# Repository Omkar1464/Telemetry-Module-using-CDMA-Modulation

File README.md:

# Long Range Telemetry Module (Phase-I)

[-purple.svg)](#firmware-architecture--timing)

> **B.Tech Phase-I Project Report & Codebase**  
> **Department of Electronics Engineering**, Sardar Vallabhbhai National Institute of Technology (SVNIT), Surat  
> **Academic Year:** 2025–26 | **Project Group:** G60  
> **Project Guide:** Dr. Suresh Dahiya (Assistant Professor, DoECE)  
> **Authors:** Moksha Parikh (`U23EC001`), Ridham Chaudhary (`U23EC030`), Omkar Sinh (`U23EC048`)

---

## 📌 Overview

This repository contains the embedded firmware, circuit schematics, simulation models, and validation benchmarks for the **Long Range Telemetry Module (Phase-I)** designed for high-altitude drone and UAV/CanSat payload communication.

Operating under the severe resource constraints of an 8-bit **ATmega328P** microcontroller (16 MHz clock, 2 KB SRAM), the system implements a **Direct Sequence Spread Spectrum (DSSS) / Code Division Multiple Access (CDMA)** baseband transmitter alongside a discrete 433 MHz RF front-end architecture.

### Key Capabilities
- **Dual-Channel CDMA Modulation:**
  - **In-Phase (I) Channel:** Carries GPS navigation data ($f_d = 100\text{ Hz}$) spread by a 1000-chip PRN sequence ($N = 1000$, theoretical processing gain $G_p = 30\text{ dB}$).
  - **Quadrature (Q) Channel:** Carries high-rate environmental telemetry ($f_d = 10\text{ kHz}$) spread by a 10-chip sequence ($N = 10$).
- **Cycle-Accurate 100 kHz Baseband Chip Rate:** $10.0\ \mu\text{s}$ per chip generated through Direct Port Manipulation (DPM), interrupt jitter elimination, and deterministic cycle calibration.
- **RF Front-End Design & Simulation:** Colpitts Local Oscillator (MPSH10 BJT) and dual-gate MOSFET (BF998) mixer stage simulated in NI Multisim and laid out on a custom 2-layer mixed-signal PCB in KiCad.

---

## 🏗️ System Architecture

```
                       +------------------------------+
                       |      2.5V - 3V Battery       |
                       +--------------+---------------+
                                      |
                            [DC-DC Boost Converter]
                                      |
                 +--------------------+--------------------+
                 | (3.3V / 5V Logic)                       | (Vcc RF)
                 v                                         v
+------------------------------------+    +----------------------------------+
|           Sensors & Inputs         |    |        Discrete RF Chain         |
| - u-blox NEO-6M GPS (UART @ 9600)  |    | - MPSH10 Colpitts LO (~358 MHz)  |
| - SHT-40 Humidity & Temp (I2C)     |    | - Dual BF998 MOSFET Mixers       |
| - PT1000-S Platinum RTD (I2C)      |    | - SAW Filter FL1 (433.92 MHz)    |
| - On-board NTC Thermistor (ADC)    |    | - RD01MUS2B RF Power Amplifier   |
+-----------------+------------------+    | - Pi-Matching Network & SMA Port |
                  |                        +-----------------+----------------+
                  v                                          ^
+------------------------------------+                       |
|       ATmega328P Controller        |                       |
| - LFSR PRN Generator (10-bit)      |                       |
| - 8x Bit-Packed Memory Storage     |                       |
| - Single-Cycle Port Writes (DPM)   |                       |
+--------+--------------------+------+                       |
         | (Dout-1: I-Chan)   | (Dout-2: Q-Chan)             |
         +--------------------+------------------------------+
```

---

## 📂 Repository File Structure

| Folder / File | Description |
| :--- | :--- |
| `GPS-Neo6M/` | Arduino firmware for NEO-6M GPS NMEA sentence extraction, checksum validation, and coordinate parsing using TinyGPS++. |
| `I_trail/` & `I_trial1/` | Baseband firmware implementation for the I-Channel (1000-chip LFSR generation, bit-packing, cycle-accurate delay loops). |
| `Q_trail/` | Baseband firmware implementation for the Q-Channel (10-chip array spreading code, corrected timing loops). |
| `task1/` & `task2/` | Firmware test suites, sensor serialization routines, and hardware debugging logs. |
| `BF998 MOSFET LIB/` | Spice simulation libraries and component footprints for the BF998 dual-gate N-channel MOSFET. |
| `Datasheet/` | Technical documentation and datasheets for active and passive components (MPSH10, BF998, RD01MUS2B, NEO-6M, SHT-40). |
| `CDMA transferring rate.pdf` | Documentation on CDMA transmission speed, spreading factors, and modulation characteristics. |
| `G48- Update-LO Simulation...` | Report and simulation data for the Local Oscillator circuit. |
| `Design1.ms14` | NI Multisim top-level schematic and RF modulator simulation circuit. |
| `L_oscillator.ms14` | NI Multisim Colpitts oscillator simulation model. |
| `d2.ms14` & `d2out.scp` | Multisim circuit simulation and oscilloscope graph captures. |
| `oscillator.cir` | SPICE netlist for the Colpitts Local Oscillator stage. |

---

## ⚡ Firmware & Timing Engineering

### 1. Memory Optimization (8× SRAM Reduction)
The ATmega328P has only 2 KB of SRAM. Allocating 1000 chips as individual `uint8_t` bytes would consume 1000 bytes (almost 50% of total SRAM):
- **Solution:** Bit-packing stores 8 chips per byte, reducing the 1000-chip array to just **125 bytes** (`uint8_t I_CDMA_PACKED[125]`).
- **LFSR PRN Generator:** Generated dynamically at startup via a 10-bit LFSR using primitive polynomial $x_n = x_{n-10} \oplus x_{n-7}$ with initial seed `0x02DF`, eliminating large hardcoded arrays in flash memory.

### 2. Elimination of Interrupt Jitter & Direct Port Manipulation
- Standard Arduino `digitalWrite()` requires ~50–60 clock cycles.
- **Direct Port Manipulation (DPM)** writes directly to `PORTB`, changing pin states in a single clock cycle ($62.5\text{ ns}$ at $16\text{ MHz}$):
  ```cpp
  PORTB |=  (1 << PORTB2); // Set Pin 10 HIGH (1 cycle)
  PORTB &= ~(1 << PORTB2); // Set Pin 10 LOW  (1 cycle)
  ```
- The Arduino core timer (`Timer0`) introduces up to $2\ \mu\text{s}$ interrupt jitter every $1.024\text{ ms}$. This is eliminated by calling `noInterrupts()` before entering the continuous transmission loop.

### 3. Cycle-Accurate Calibration Loop
To achieve a target chip rate of $f_c = 100\text{ kHz}$ ($T_c = 10.0\ \mu\text{s}$):
$$\text{Total Clock Budget} = 10.0\ \mu\text{s} \times 16\text{ MHz} = 160\text{ cycles}$$
Accounting for loop overhead, bit shifting, and DPM write (~3 cycles), the calibrated delay is:
```cpp
__builtin_avr_delay_cycles(157); // 157 cycles @ 16 MHz = 9.81 us
```

---

## 🔬 Hardware Verification & Measurement Results

Because random PRN sequences produce consecutive identical chips that cause auto-counter readouts to fluctuate on oscilloscopes (the *PRN frequency illusion*), a **DSO Calibration Mode** with an alternating `0xAA` (`10101010b`) test pattern was used for hardware verification:
$$f_{\text{DSO}} = \frac{f_c}{2} = 50.0\text{ kHz}$$

| Parameter | Theoretical / Target | Measured (Tektronix DSO) | Timing Deviation |
| :--- | :---: | :---: | :---: |
| **I-Channel Baseline (Alternating)** | $50.0\text{ kHz}$ ($20.0\ \mu\text{s}$ period) | $45.89\text{ kHz}$ ($22.20\ \mu\text{s}$) | $-8.22\%$ |
| **Q-Channel Baseline (Post-Correction)**| $50.0\text{ kHz}$ ($20.0\ \mu\text{s}$ period) | $45.03\text{ kHz}$ ($22.20\ \mu\text{s}$) | $-9.94\%$ |
| **Single Chip Duration** | $10.0\ \mu\text{s}$ | $\approx 11.10\ \mu\text{s}$ | Within $\pm 10\%$ SDR budget |
| **Logic Level (Rail-to-Rail)** | $5.0\text{ V}$ | $5.60\text{ V} - 7.60\text{ V}_{\text{pk-pk}}$* | Rail-to-rail confirmed |

*\*Note: High peak-to-peak reading on the DSO is attributed to probe measurement ringing on the nanosecond-fast DPM rise/fall edges.*

---

## 📡 RF Front-End & PCB Design

- **Colpitts Local Oscillator:** Built with an **MPSH10 NPN BJT** ($f_T \approx 650\text{ MHz}$).
  $$C_{eq} = \frac{C_1 C_2}{C_1 + C_2} = \frac{22 \times 22}{22 + 22} = 11\text{ pF}$$
  $$f_0 = \frac{1}{2\pi \sqrt{L_2 \cdot C_{eq}}} = \frac{1}{2\pi \sqrt{0.18\ \mu\text{H} \cdot 11\text{ pF}}} \approx 358\text{ MHz}$$
- **Multisim Simulation:** Sustained oscillation confirmed at $357\text{ MHz}$ with an output amplitude of $3.54\text{ V}_{\text{pk}}$ ($< 0.3\%$ discrepancy from analytical equations).
- **Custom PCB (KiCad):** 2-layer mixed-signal board featuring segregated functional partitions:
  - Top-Right: NEO-6M GPS module placed near the perimeter for antenna clearance.
  - Top-Center: ATmega328P TQFP-32 with SPI header and adjacent clock crystal.
  - Left: Power management (NCP1640T, HT3608) and Local Oscillator.
  - Bottom-Right: RF chain with dual BF998 mixers, SAW filter, RD01MUS2B PA, and SMA connector backed by a solid stitched ground plane.

---

## 👥 Authors & Academic Affiliation

* **Moksha Parikh** (`U23EC001`) -- [GitHub Profile](https://github.com/mokshaparikh11)   
* **Ridham Chaudhary** (`U23EC030`) — [GitHub Profile](https://github.com/chaudharyridham)  
* **Omkar Sinh** (`U23EC048`) — [GitHub Profile](https://github.com/Omkar1464)  

**Project Guide:**  
**Dr. Suresh Dahiya**, Assistant Professor, Department of Electronics and Communication Engineering  
**Sardar Vallabhbhai National Institute of Technology (SVNIT)**, Surat, Gujarat, India.

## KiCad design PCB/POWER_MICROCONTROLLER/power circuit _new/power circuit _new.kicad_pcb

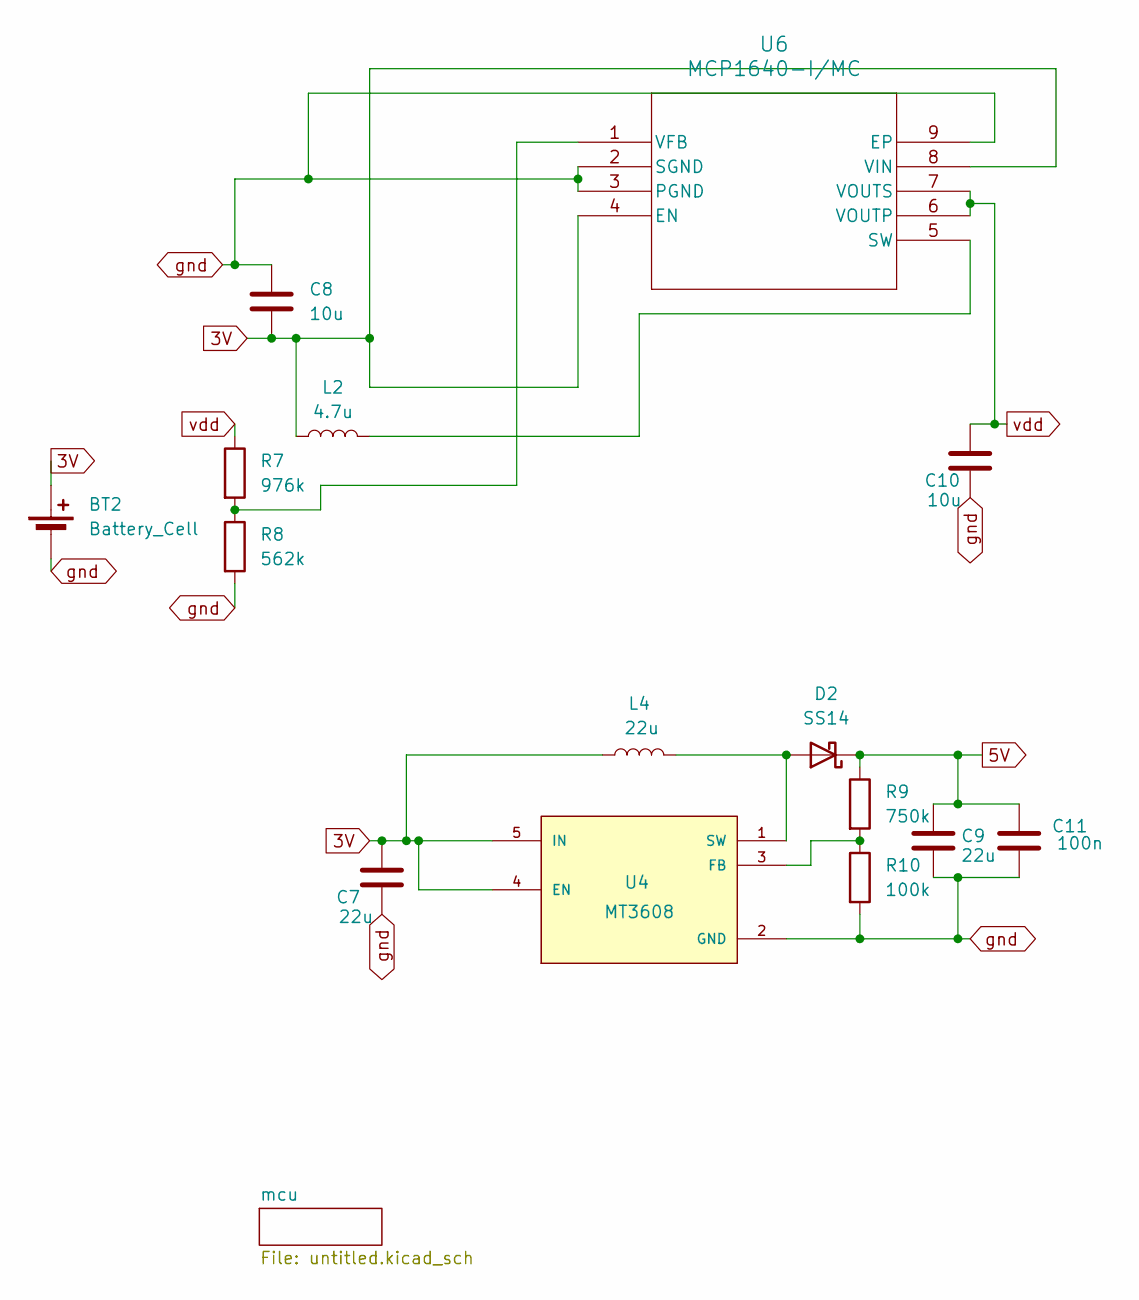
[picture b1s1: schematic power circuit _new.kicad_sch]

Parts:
BT2: Battery_Cell; SolderWire-0.25sqmm_1x02_P4.2mm_D0.65mm_OD1.7mm_Relief2x
C7, C9: 22u; C_0603_1608Metric
C8, C10: 10u; C_0603_1608Metric
C11: 100n; C_0603_1608Metric
D2: SS14; D_SMA
L2: 4.7u; L_0603_1608Metric
L4: 22u; L_0603_1608Metric
R7: 976k; R_0603_1608Metric
R8: 562k; R_0603_1608Metric
R9: 750k; R_0603_1608Metric
R10: 100k; R_0603_1608Metric
U4: MT3608; SOT95P280X145-6N; PARTREV 1.0
U6: MCP1640-I/MC; DFN8_2x3MC_MCH

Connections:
3V: BT2.1 (+), C7.1, C8.1, L2.1, L4.1, U4.4 (EN), U4.5 (IN), U6.4 (EN), U6.8 (VIN)
5V: C9.1, C11.1, D2.1 (K), R9.1
unnamed: D2.2 (A), L4.2, U4.1 (SW)
unnamed: R9.2, R10.1, U4.3 (FB)
unnamed: L2.2, U6.5 (SW)
unnamed: R7.2, R8.1, U6.1 (VFB)
gnd: BT2.2 (-), C7.2, C8.2, C9.2, C10.2, C11.2, R8.2, R10.2, U4.2 (GND), U6.2 (SGND), U6.3 (PGND), U6.9 (EP); also elsewhere on the board
vdd: C10.1, R7.1, U6.6 (VOUTP), U6.7 (VOUTS); also elsewhere on the board

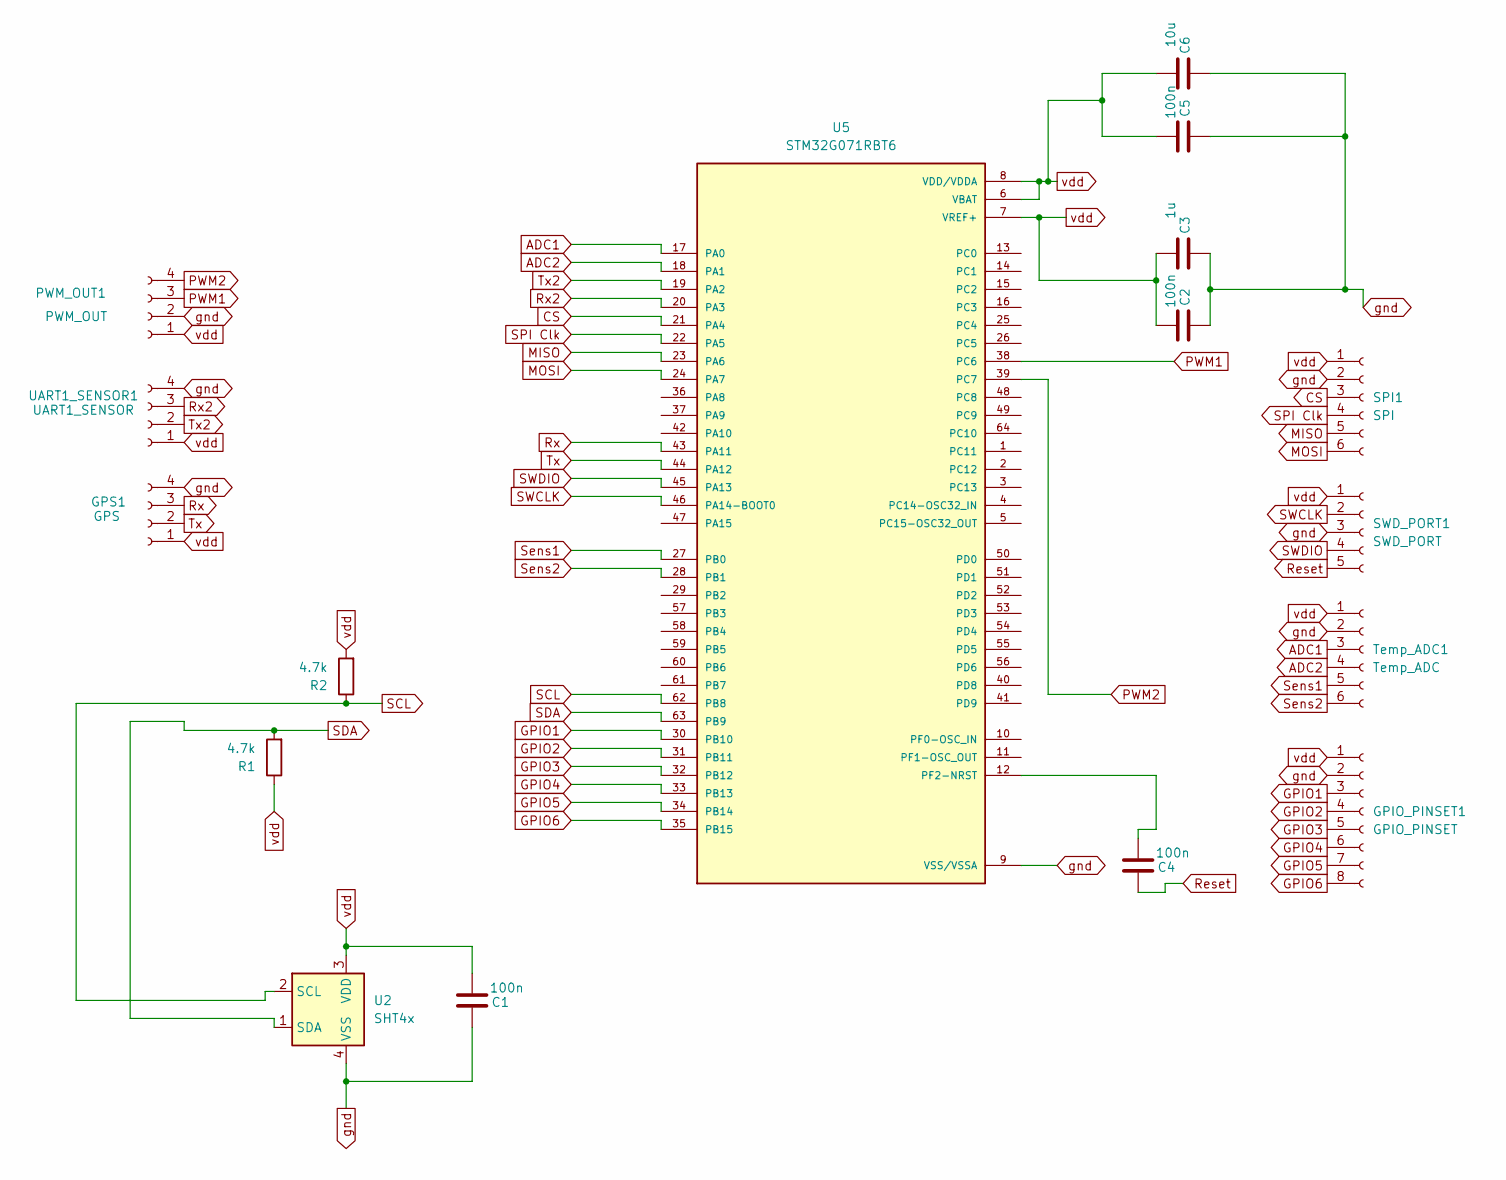
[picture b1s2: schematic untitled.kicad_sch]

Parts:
C1, C2, C4, C5: 100n; C_0603_1608Metric
C3: 1u; C_0603_1608Metric
C6: 10u; C_0603_1608Metric
GPIO_PINSET1: GPIO_PINSET; PinSocket_1x08_P2.54mm_Vertical
GPS1: GPS; PinSocket_1x04_P2.54mm_Vertical
PWM_OUT1: PWM_OUT; PinSocket_1x04_P2.54mm_Vertical
R1, R2: 4.7k; R_0603_1608Metric
SPI1: SPI; PinSocket_1x06_P2.54mm_Vertical
SWD_PORT1: SWD_PORT; PinSocket_1x05_P2.54mm_Vertical
Temp_ADC1: Temp_ADC; PinSocket_1x06_P2.54mm_Vertical
U2: SHT4x; Sensirion_DFN-4_1.5x1.5mm_P0.8mm_SHT4x_NoCentralPad
U5: STM32G071RBT6; LQFP-64_7x7mm_P0.4mm; PARTREV 2
UART1_SENSOR1: UART1_SENSOR; PinSocket_1x04_P2.54mm_Vertical

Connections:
ADC1: Temp_ADC1.3, U5.17 (PA0)
ADC2: Temp_ADC1.4, U5.18 (PA1)
CS: SPI1.3, U5.21 (PA4)
GPIO1: GPIO_PINSET1.3, U5.30 (PB10)
GPIO2: GPIO_PINSET1.4, U5.31 (PB11)
GPIO3: GPIO_PINSET1.5, U5.32 (PB12)
GPIO4: GPIO_PINSET1.6, U5.33 (PB13)
GPIO5: GPIO_PINSET1.7, U5.34 (PB14)
GPIO6: GPIO_PINSET1.8, U5.35 (PB15)
MISO: SPI1.5, U5.23 (PA6)
MOSI: SPI1.6, U5.24 (PA7)
unnamed: C4.2, U5.12 (PF2-NRST)
PWM1: PWM_OUT1.3, U5.38 (PC6)
PWM2: PWM_OUT1.4, U5.39 (PC7)
Reset: C4.1, SWD_PORT1.5
Rx: GPS1.3, U5.43 (PA11)
Rx2: U5.20 (PA3), UART1_SENSOR1.3
SCL: R2.1, U2.2 (SCL), U5.62 (PB8)
SDA: R1.2, U2.1 (SDA), U5.63 (PB9)
SPI Clk: SPI1.4, U5.22 (PA5)
SWCLK: SWD_PORT1.2, U5.46 (PA14-BOOT0)
SWDIO: SWD_PORT1.4, U5.45 (PA13)
Sens1: Temp_ADC1.5, U5.27 (PB0)
Sens2: Temp_ADC1.6, U5.28 (PB1)
Tx: GPS1.2, U5.44 (PA12)
Tx2: U5.19 (PA2), UART1_SENSOR1.2
gnd: C1.1, C2.1, C3.1, C5.1, C6.1, GPIO_PINSET1.2, GPS1.4, PWM_OUT1.2, SPI1.2, SWD_PORT1.3, Temp_ADC1.2, U2.4 (VSS), U5.9 (VSS/VSSA), UART1_SENSOR1.4; also elsewhere on the board
vdd: C1.2, C2.2, C3.2, C5.2, C6.2, GPIO_PINSET1.1, GPS1.1, PWM_OUT1.1, R1.1, R2.2, SPI1.1, SWD_PORT1.1, Temp_ADC1.1, U2.3 (VDD), U5.6 (VBAT), U5.7 (VREF+), U5.8 (VDD/VDDA), UART1_SENSOR1.1; also elsewhere on the board

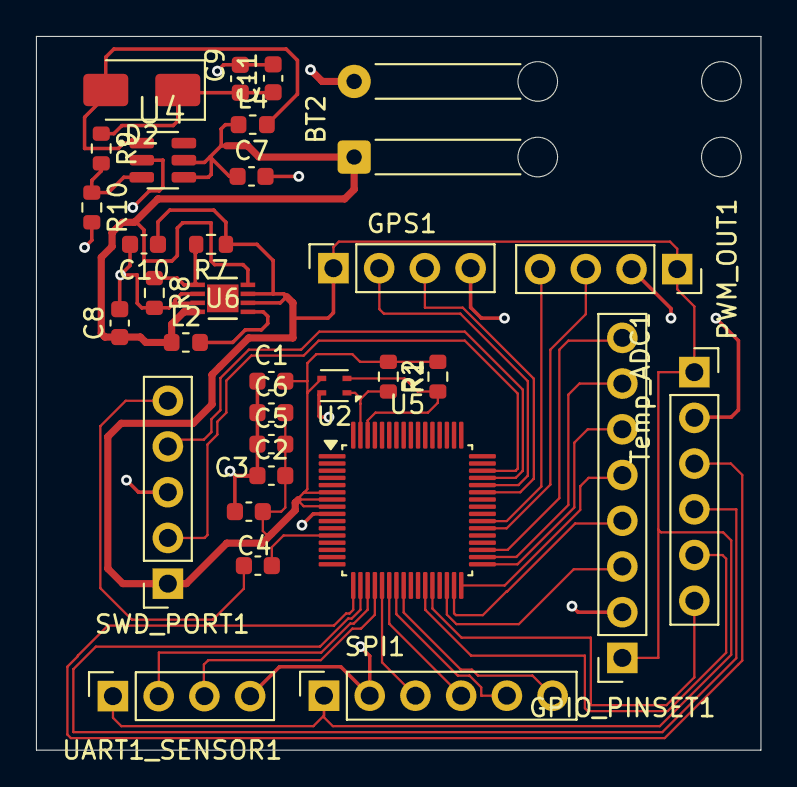
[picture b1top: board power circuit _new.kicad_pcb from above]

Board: 2 copper layers, 40.2 x 39.7 mm, 32 parts (0 on the bottom side), 34 nets.

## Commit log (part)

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2026-01-23 Readme
2026-01-23 23/1
2026-01-28 design2
2026-02-17 vnjbjk
2026-02-17 fghcf
2026-02-19 flsfs
2026-02-19 cslkc';sl
